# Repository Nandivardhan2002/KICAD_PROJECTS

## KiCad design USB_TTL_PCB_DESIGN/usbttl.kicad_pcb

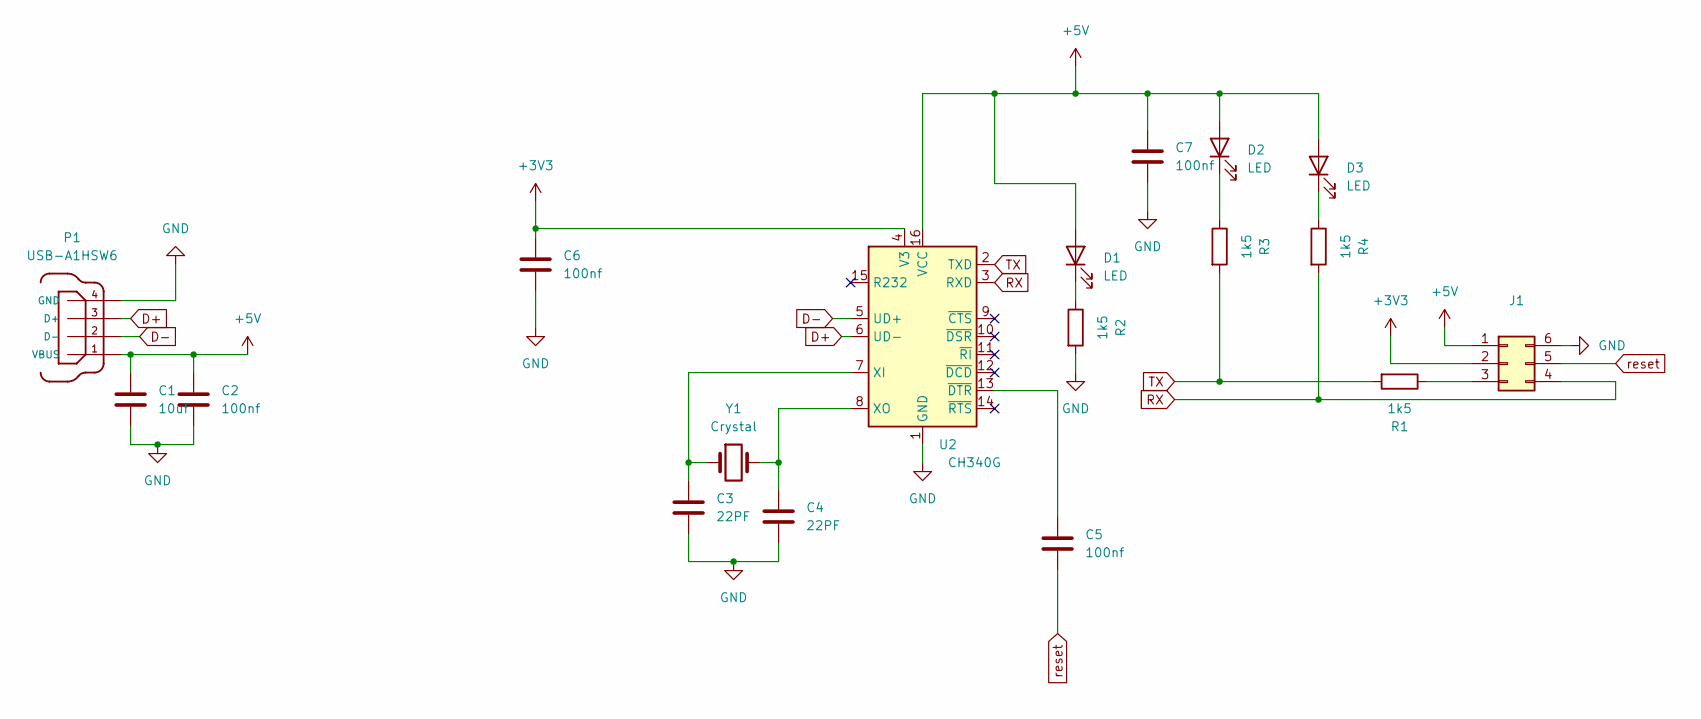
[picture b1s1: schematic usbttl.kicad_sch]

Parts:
C1: 10uf; C_0201_0603Metric
C2, C5, C6, C7: 100nf; C_0201_0603Metric
C3, C4: 22PF; C_0201_0603Metric
D1, D2, D3: LED; LED_0201_0603Metric
J1: Conn_02x03_Counter_Clockwise; PinHeader_2x03_P1.00mm_Vertical
P1: USB-A1HSW6; USB_A_CNCTech_1001-011-01101_Horizontal
R1, R2, R3, R4: 1k5; R_0201_0603Metric
U2: CH340G; SOIC-16_3.9x9.9mm_P1.27mm
Y1: Crystal; Crystal_HC18-U_Vertical

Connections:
+3V3: C6.1, J1.2, U2.4 (V3)
+5V: C1.1, C2.1, C7.1, D1.2 (A), D2.2 (A), D3.2 (A), J1.1, P1.1 (VBUS), U2.16 (VCC)
D+: P1.3 (D+), U2.6 (UD-)
D-: P1.2 (D-), U2.5 (UD+)
GND: C1.2, C2.2, C3.2, C4.2, C6.2, C7.2, J1.6, P1.4 (GND), R2.2, U2.1 (GND)
unnamed: D1.1 (K), R2.1
unnamed: D2.1 (K), R3.1
unnamed: D3.1 (K), R4.1
unnamed: J1.3, R1.1
unnamed: C3.1, U2.7 (XI), Y1.1
unnamed: C4.1, U2.8 (XO), Y1.2
unnamed: C5.1, U2.13 (~DTR)
RX: J1.4, R4.2, U2.3 (RXD)
TX: R1.2, R3.2, U2.2 (TXD)
reset: C5.2, J1.5

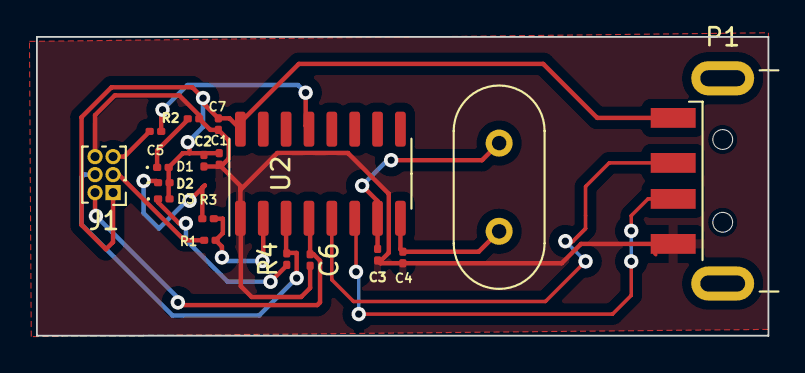
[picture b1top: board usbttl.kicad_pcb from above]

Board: 2 copper layers, 40.6 x 16.6 mm, 18 parts (0 on the bottom side), 15 nets.
